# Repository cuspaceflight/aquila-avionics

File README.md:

# Aquila Avionics
Schematics and firmware for Aquila flight computer.

## Functions
* **Altimetry** - Accurately estimate altitude with barometer, GPS and accelerometer
* **Recovery** - Activate pyrotechnics to deploy parachute stages at appropriate points during descent
*  **Data logging** - Log altitude data and other parameters for post-flight analysis
* **Telemetry** - Transmit data to a ground station during flight as a backup should the vehicle be lost
* **Location** - Continually transmit location after landing to aid finding the vehicle

## Specifications
* **Mass** -  2kg
* **Acceleration** - 30g
* **Altitude** - 150km
* **Speed** - 1500m/s
* **Flexibility** - Exact flight and recovery profile is TBC
*  **Budget** - �150

# Overview
What follows here is a very brief overview of the design, broken down by component. It's aim is to familiarise the reader with what this project includes and some of the decisions made.
## Batteries
The computer is designed to run from two 18650 Li-Ions in series. A battery management chip monitors the cell voltages and automatically balances them if necessary. There is no onboard charger, so batteries must be charged separately before installation/flights. Ideally cells with built-in under-volt protection should be used. The battery holders are physically mounted to the board (but will be mechanically supported by additional hardware). Power can be switched on and off via a screw terminal.  To connect the batteries to the rest of the board, a jumper is secured between the two terminals. A potential divider allows the microcontroller to directly monitor the battery voltages.

Additionally, a 3V CR2032 type cell is mounted to the board. This maintains real time clocks in the microcontroller and GPS receiver, improving resilience against power cycle events during flight.
## Power supplies
The board has two power supplies: 3.3V 3A and 5V 3A. The 3.3V supply powers most of the electronics on the board and is permanently on. The 5V supply is dedicated to pyrotechnics and servos as required by the recovery system. It is switched on and off by the microcontroller to conserve power when not needed and as a safety layer. A terminal is provided for an external safety switch. When shorted, this terminal disables the pyro power supply, eliminating the risk of unintentionally activating pyrotechnics during any activities leading up to launch.
## Sensors
### Barometer
A barometer is mounted on the board to measure atmospheric pressure. This is particularly useful during descent to deploy parachute stages at appropriate altitudes close to the ground. The model used is a MS5611-01BA03. It has a resolution on the order of tenths of millibar, but a minimum pressure of 10 millibar limits it's usefulness to below 30 km altitude.
### GPS
A U-blox MAX-M8Q receiver is included for completeness. CoCom regulations limit the operation of civilian GPS chips faster than 1000 knots (~500 m/s) and above 18 km, both of which will be exceeded early in Griffin's flight profile. Therefore the GPS will not be relied on for navigational purposes, but purely for data collection. It may be the case that once the rocket slows below 1000 knots near apogee, a fix can once again be acquired. This is uncertain as the manufacturer does not specify behaviour at these extremes.

An additional Low-Noise Amplifier and band-pass filter are included in the signal path as antenna challenges and telemetry radio interference will degrade signal quality.
### Accelerometer
The most important sensor for navigation and apogee deployment is the accelerometer. An inertial navigation system will be implemented to estimate the vehicle's velocity and altitude based on accelerometer readings. The double integration of acceleration to velocity leads to errors on the order of time squared, so it is imperative the accelerometer readings are low noise and very stable. Combined with this requirement, a high g range is required as the rocket will accelerate at up to 30g at some points.  An Analog Devices ADXL357 is chosen. It boasts 20 bit resolution, ultra-low noise and high bias stability with a range of +/- 40g.
## Telemetry
An Si4463 radio transceiver provides a bi-directional radio link with a ground station. This will be useful for configuring the computer during launch preparations as well as backing up as much data as possible should the vehicle be lost. A secondary purpose for the radio will be locating the vehicle after a successful recovery. The current setup is designed for operation in the 915 MHz ISM band, subject to regulatory compliance.
## Interfaces
Connectors on the board include: 
* **female SMA** for GPS antenna
* **female SMA** for telemetry antenna
* **6-way Molex Nano-Fit** for a separate, remote, barometer, in case structural limitations prevent the avionics bay being vented to the atmosphere
* **6-way Molex Nano-Fit** for up to four servo motors
* **4x 2-way screw terminal** for up to four pyrotechnics
* **Micro USB** for programming and serial communication

The pyro channels can provide 5V at 1A continuous as limited by the FETs, 3A peak as limited by the power supply. They also include individual continuity measurement by draining approximately 50uA through the pyro.
## Microcontroller
A Teensy 4.1 was selected as the microcontroller. It is based around an ARM Cortex-M7 running at 600MHz. The first reason for this choice is that it includes many features we would only have to implement ourselves such as a real time clock, MicroSD storage, USB interface etc. Secondly, it is compatible with the Arduino ecosystem, granting access to many existing libraries and improving access to the firmware for CUSF members.
## Antennas
Antennas are an area of ongoing research, hence nothing has been included in this repo yet. Carbon-fibre reinforced polymer (CFRP) construction precludes antennas being mounted inside the rocket body, and extreme aerodynamic and aerothermal loads make any kind of protruding antenna impossible. This leaves the only possible solution as conformal patch antenna arrays. Methods to design and optimise these antennas and feed networks are currently being developed. See <https://github.com/cuspaceflight/aperture>.

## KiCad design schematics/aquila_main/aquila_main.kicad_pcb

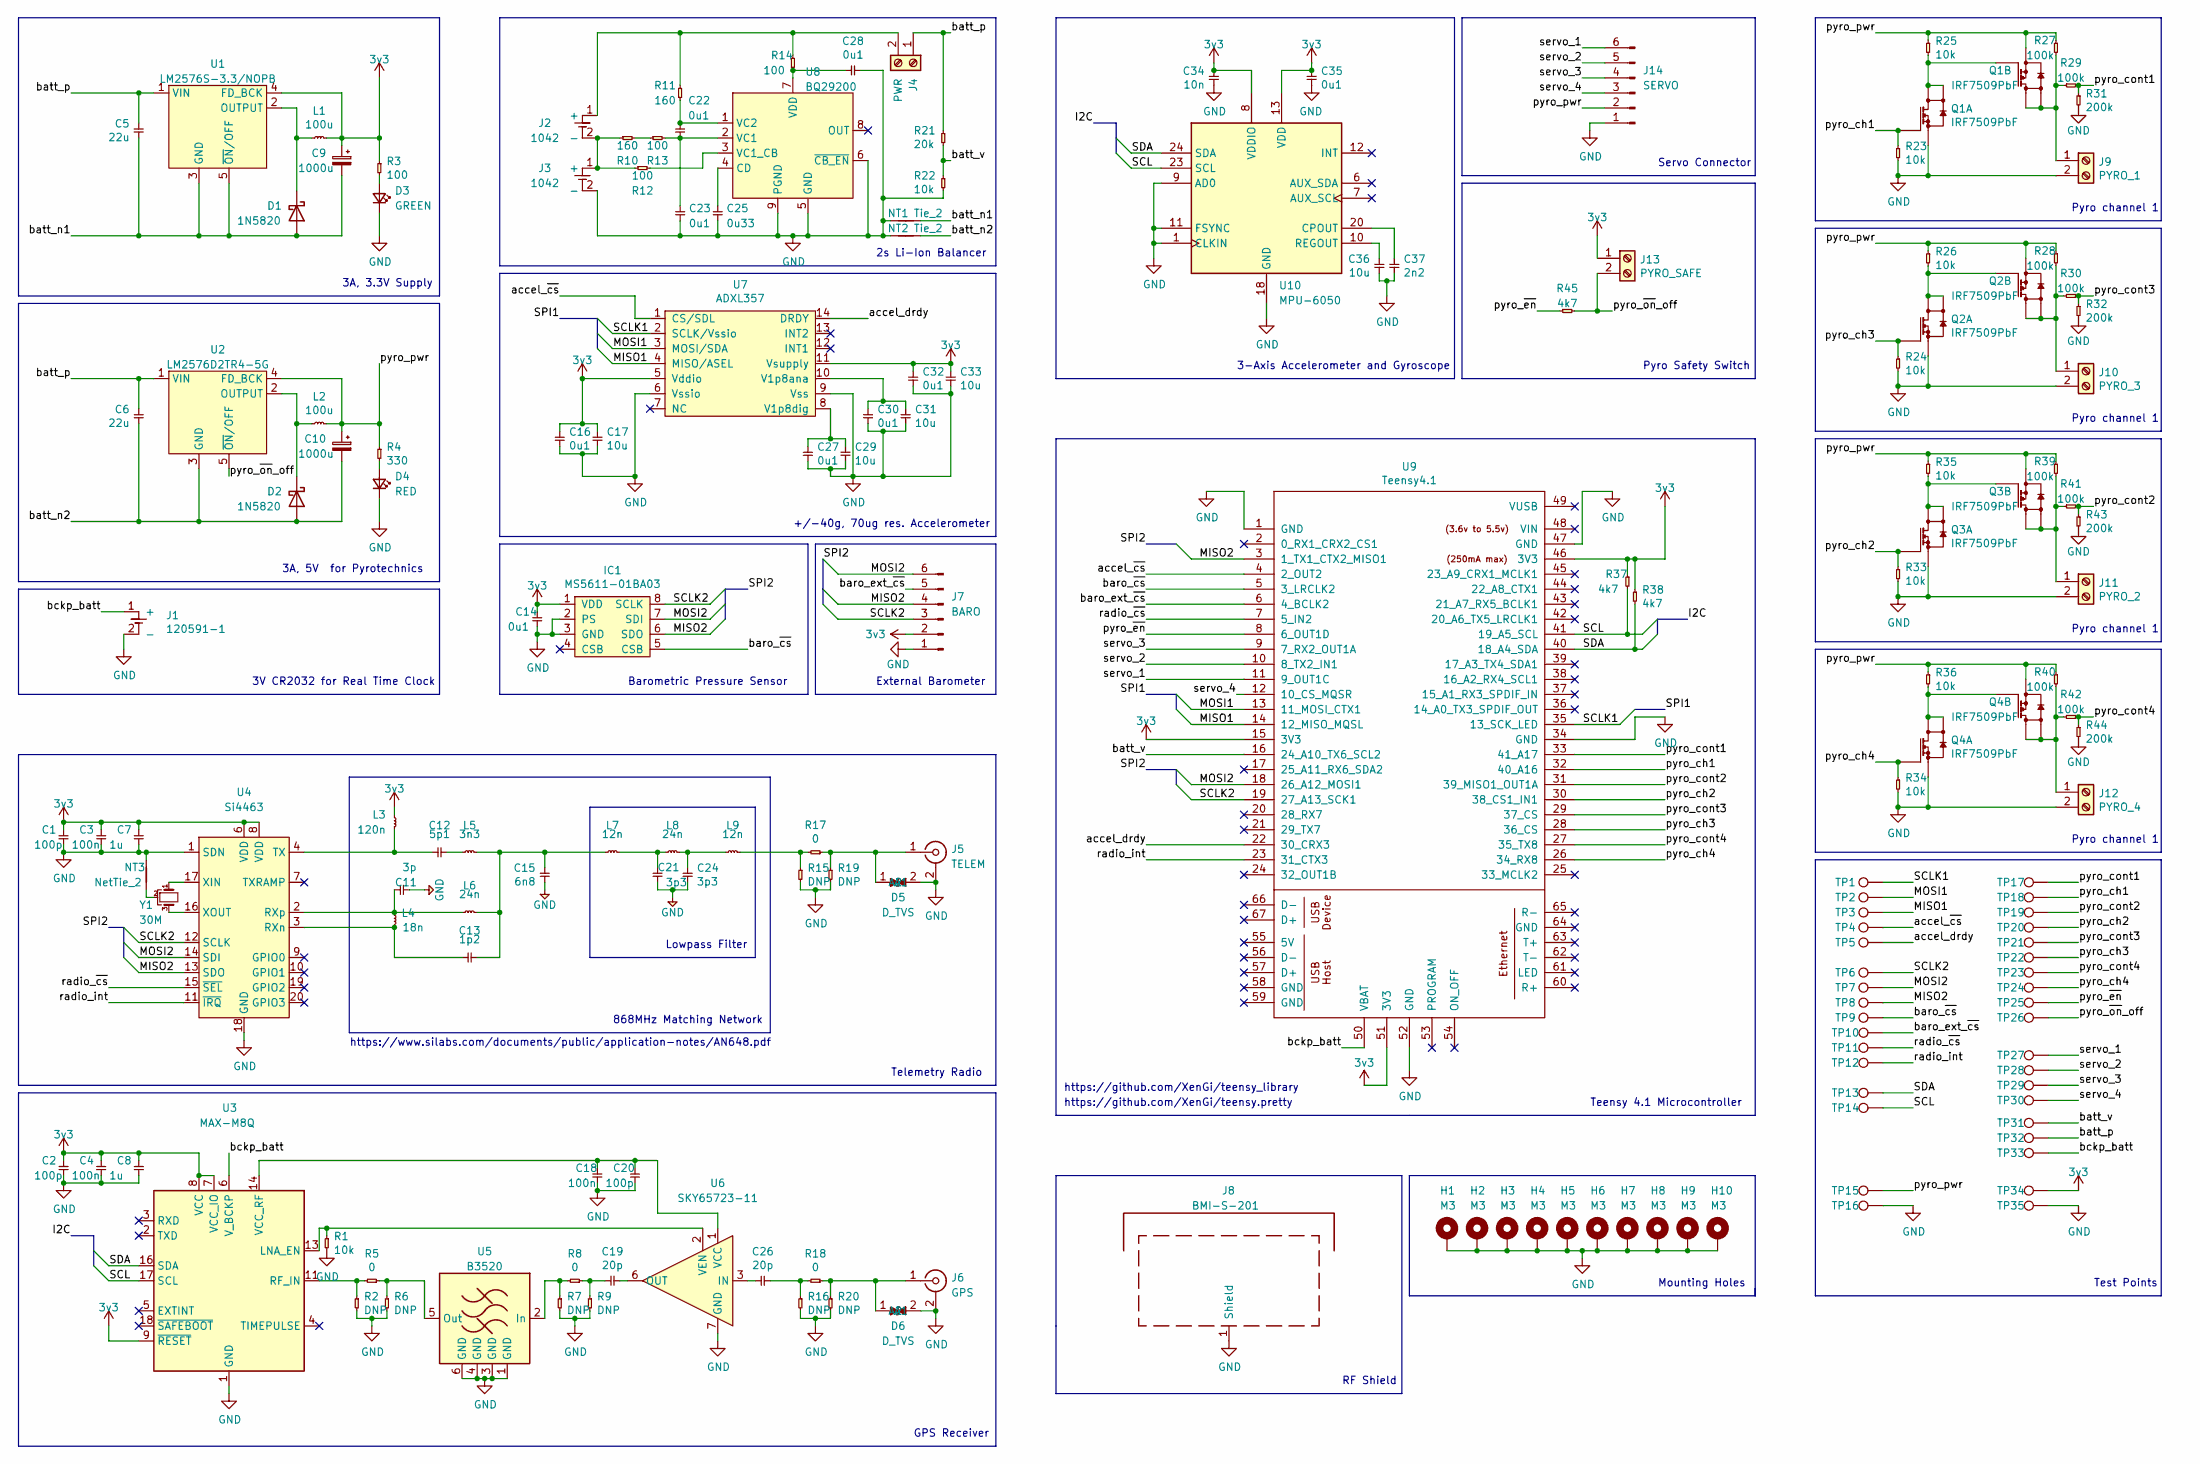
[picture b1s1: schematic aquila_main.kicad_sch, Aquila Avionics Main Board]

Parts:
C1, C2, C20: 100p; C_0402_1005Metric
C3, C4, C18: 100n; C_0402_1005Metric
C5, C6: 22u; CP_Radial_D6.3mm_P2.50mm; Farnell 9452710
C7, C8: 1u; C_0402_1005Metric
C9, C10: 1000u; CP_Radial_D8.0mm_P3.50mm; Farnell 2760327
C11: 3p; C_0402_1005Metric; Farnell 1758933
C12: 5p1; C_0402_1005Metric; Farnell 2781439
C13: 1p2; C_0402_1005Metric; Farnell 3369062
C14, C16, C22, C23, C27, C28, C30, C32, C35: 0u1; C_0402_1005Metric
C15: 6n8; C_0402_1005Metric; Farnell 2627370
C17, C29, C31, C33, C36: 10u; C_0402_1005Metric
C19, C26: 20p; C_0402_1005Metric
C21, C24: 3p3; C_0402_1005Metric; Farnell 2627406
C25: 0u33; C_0402_1005Metric
C34: 10n; C_0402_1005Metric
C37: 2n2; C_0402_1005Metric
D1, D2: 1N5820; D_DO-201AD_P15.24mm_Horizontal; Farnell 2317410
D3: GREEN; D_0603_1608Metric; Farnell 3796304
D4: RED; D_0603_1608Metric; Farnell 3796306
D5, D6: D_TVS; D_0402_1005Metric; Farnell 2368169
H1, H2, H3, H4, H5, H6, H7, H8, H9, H10: M3; MountingHole_3.2mm_M3_DIN965_Pad
IC1: MS5611-01BA03; MS5611; Farnell 2362662
J1: 120591-1; DigiKey A99328-ND
J2, J3: 1042; DigiKey 36-1042P-ND
J4: PWR; MP_2.54_screw_terminal_2x1; Farnell 3817460
J5: TELEM; SMA_VERT; Mouser 960-PCB.SMAFST.J.AHT
J6: GPS; SMA_VERT; Mouser 960-PCB.SMAFST.J.AHT
J7: BARO; molex_nano_fit_x6_105310-1106; Farnell 2820682
J8: BMI-S-201; Farnell 2497715
J9: PYRO_1; MP_2.54_screw_terminal_2x1; Farnell 3817460
J10: PYRO_3; MP_2.54_screw_terminal_2x1; Farnell 3817460
J11: PYRO_2; MP_2.54_screw_terminal_2x1; Farnell 3817460
J12: PYRO_4; MP_2.54_screw_terminal_2x1; Farnell 3817460
J13: PYRO_SAFE; MP_2.54_screw_terminal_2x1; Farnell 3817460
J14: SERVO; molex_nano_fit_x6_105310-1106; Farnell 2820682
L1, L2: 100u; L_MP0028_124_125_127; Farnell 2288307
L3: 120n; L_0402_1005Metric; Farnell 3471254
L4: 18n; L_0402_1005Metric; Farnell 1343084
L5: 3n3; L_0402_1005Metric; Farnell 1343068
L6, L8: 24n; L_0402_1005Metric; Farnell 3263549
L7, L9: 12n; L_0402_1005Metric; Farnell 1343082
NT1, NT2: Tie_2; NetTie-2_THT_Pad1.0mm
NT3: NetTie_2; NetTie-2_SMD_Pad0.5mm
Q1, Q2, Q3, Q4: IRF7509PbF; Farnell 1611421
R1, R22, R23, R24, R25, R26, R33, R34, R35, R36: 10k; R_0402_1005Metric
R2, R6, R7, R9, R15, R16, R19, R20: DNP; R_0402_1005Metric
R3, R12, R13, R14: 100; R_0402_1005Metric
R4: 330; R_0402_1005Metric
R5, R8, R17, R18: 0; R_0402_1005Metric
R10, R11: 160; R_0402_1005Metric
R21: 20k; R_0402_1005Metric
R27, R28, R29, R30, R39, R40, R41, R42: 100k; R_0402_1005Metric
R31, R32, R43, R44: 200k; R_0402_1005Metric
R37, R38, R45: 4k7; R_0402_1005Metric
TP1, TP2, TP3, TP4, TP5, TP6, TP7, TP8, TP9, TP10, TP11, TP12, TP13, TP14, TP15, TP16, TP17, TP18, TP19, TP20, TP21, TP22, TP23, TP24, TP25, TP26, TP27, TP28, TP29, TP30, TP31, TP32, TP33, TP34, TP35: TestPoint; TestPoint_Pad_D1.0mm
U1: LM2576S-3.3/NOPB; TO-236_5; Farnell 3008143
U2: LM2576D2TR4-5G; TO-236_5; Farnell 2534166
U3: MAX-M8Q
U4: Si4463; QFN-20-1EP_4x4mm_P0.5mm_EP2.6x2.6mm_ThermalVias; DigiKey 336-4346-1-ND
U5: B3520; DigiKey 495-2363-1-ND
U6: SKY65723-11; SKY65723-81; Mouser 873-SKY65723-81
U7: ADXL357; DigiKey 505-ADXL357BEZ-ND
U8: BQ29200; VSOP-8; Farnell 2383074
U9: Teensy4.1; Teensy41; DigiKey 223-1622-1-ND
U10: MPU-6050; InvenSense_QFN-24_4x4mm_P0.5mm; Farnell 3769961
Y1: 30M; crystal_ABM8; Farnell 3228351

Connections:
+3V3: C1.1, C2.1, C3.1, C4.1, C7.1, C8.1, C9.1, C14.1, C16.1, C17.1, C32.1, C33.1, C34.1, C35.1, IC1.1 (VDD), J7.2, J13.1, L1.2, L3.1, R3.1, R37.1, R38.1, TP34.1, U1.4 (FD_BCK), U3.7 (VCC_IO), U3.8 (VCC), U3.9 (~RESET), U4.6 (VDD), U4.8 (VDD), U7.5 (Vddio), U7.11 (Vsupply), U9.15 (3V3), U9.46 (3V3), U9.51 (3V3), U10.8 (VDDIO), U10.13 (VDD)
/MISO1: TP3.1, U7.4 (MISO/ASEL), U9.14 (12_MISO_MQSL)
/MISO2: IC1.6 (SDO), J7.4, TP8.1, U4.13 (SDO), U9.3 (1_TX1_CTX2_MISO1)
/MOSI1: TP2.1, U7.3 (MOSI/SDA), U9.13 (11_MOSI_CTX1)
/MOSI2: IC1.7 (SDI), J7.6, TP7.1, U4.14 (SDI), U9.18 (26_A12_MOSI1)
/SCL: R37.2, TP14.1, U3.17 (SCL), U9.41 (19_A5_SCL), U10.23 (SCL)
/SCLK1: TP1.1, U7.2 (SCLK/Vssio), U9.35 (13_SCK_LED)
/SCLK2: IC1.8 (SCLK), J7.3, TP6.1, U4.12 (SCLK), U9.19 (27_A13_SCK1)
/SDA: R38.2, TP13.1, U3.16 (SDA), U9.40 (18_A4_SDA), U10.24 (SDA)
/accel_drdy: TP5.1, U7.14 (DRDY), U9.22 (30_CRX3)
/accel_~cs: TP4.1, U7.1 (CS/SDL), U9.4 (2_OUT2)
/baro_ext_~cs: J7.5, TP10.1, U9.6 (4_BCLK2)
/baro_~cs: IC1.5 (CSB), TP9.1, U9.5 (3_LRCLK2)
/batt_n1: C5.2, C9.2, D1.2 (A), NT1.2, U1.3 (GND), U1.5 (~ON/OFF)
/batt_n2: C6.2, C10.2, D2.2 (A), NT2.2, U2.3 (GND)
/batt_p: C5.1, C6.1, J4.1, R21.1, TP32.1, U1.1 (VIN), U2.1 (VIN)
/batt_v: R21.2, R22.1, TP31.1, U9.16 (24_A10_TX6_SCL2)
/bckp_batt: J1.1 (+), TP33.1, U3.6 (V_BCKP), U9.50 (VBAT)
/pyro_ch1: Q1.2 (G1), R23.1, TP18.1, U9.32 (40_A16)
/pyro_ch2: Q3.2 (G1), R33.1, TP20.1, U9.30 (38_CS1_IN1)
/pyro_ch3: Q2.2 (G1), R24.1, TP22.1, U9.28 (36_CS)
/pyro_ch4: Q4.2 (G1), R34.1, TP24.1, U9.26 (34_RX8)
/pyro_cont1: R29.2, R31.1, TP17.1, U9.33 (41_A17)
/pyro_cont2: R41.2, R43.1, TP19.1, U9.31 (39_MISO1_OUT1A)
/pyro_cont3: R30.2, R32.1, TP21.1, U9.29 (37_CS)
/pyro_cont4: R42.2, R44.1, TP23.1, U9.27 (35_TX8)
/pyro_pwr: C10.1, J14.2, L2.2, Q1.3 (S2), Q2.3 (S2), Q3.3 (S2), Q4.3 (S2), R4.1, R25.1, R26.1, R27.1, R28.1, R35.1, R36.1, R39.1, R40.1, TP15.1, U2.4 (FD_BCK)
/pyro_~en: R45.1, TP25.1, U9.8 (6_OUT1D)
/pyro_~on_off: J13.2, R45.2, TP26.1, U2.5 (~ON/OFF)
/radio_int: TP12.1, U4.11 (~IRQ), U9.23 (31_CTX3)
/radio_~cs: TP11.1, U4.15 (~SEL), U9.7 (5_IN2)
/servo_1: J14.6, TP27.1, U9.11 (9_OUT1C)
/servo_2: J14.5, TP28.1, U9.10 (8_TX2_IN1)
/servo_3: J14.4, TP29.1, U9.9 (7_RX2_OUT1A)
/servo_4: J14.3, TP30.1, U9.12 (10_CS_MQSR)
GND: C1.2, C2.2, C3.2, C4.2, C7.2, C8.2, C11.2, C14.2, C15.2, C16.2, C17.2, C18.2, C20.2, C21.2, C23.1, C24.2, C25.1, C27.2, C28.2, C29.2, C30.2, C31.2, C32.2, C33.2, C34.2, C35.2, C36.2, C37.2, D3.1 (K), D4.1 (K), D5.2 (A2), D6.2 (A2), H1.1, H2.1, H3.1, H4.1, H5.1, H6.1, H7.1, H8.1, H9.1, H10.1, IC1.2 (PS), IC1.3 (GND), J1.2 (-), J3.2 (-), J5.2 (Ext), J6.2 (Ext), J7.1, J8.1 (Shield), J9.2, J10.2, J11.2, J12.2, J14.1, NT1.1, NT2.1, NT3.2, Q1.1 (S1), Q2.1 (S1), Q3.1 (S1), Q4.1 (S1), R1.2, R2.2, R6.2, R7.2, R9.2, R15.2, R16.2, R19.2, R20.2, R22.2, R23.2, R24.2, R31.2, R32.2, R33.2, R34.2, R43.2, R44.2, TP16.1, TP35.1, U3.1 (GND), U3.10 (GND), U3.12 (GND), U4.1 (SDN), U4.18 (GND), U4.21 (GND), U5.1 (GND), U5.3 (GND), U5.4 (GND), U5.6 (GND), U6.7 (GND), U7.6 (Vssio), U7.9 (Vss), U8.5 (GND), U8.6 (~CB_EN), U8.9 (PGND), U9.1 (GND), U9.34 (GND), U9.47 (GND), U9.52 (GND), U10.1 (CLKIN), U10.9 (AD0), U10.11 (FSYNC), U10.18 (GND)
unnamed: C11.1, L4.1, L6.1, U4.2 (RXp)
unnamed: C12.1, L3.2, U4.4 (TX)
unnamed: C12.2, L5.1
unnamed: C13.1, L4.2, U4.3 (RXn)
unnamed: C13.2, C15.1, L5.2, L6.2, L7.1
unnamed: C18.1, C20.1, U3.14 (VCC_RF), U6.1 (VCC)
unnamed: C19.1, R8.1, R9.1
unnamed: C19.2, U6.6 (OUT)
unnamed: C21.1, L7.2, L8.1
unnamed: C22.1, C23.2, R13.2, U8.2 (VC1)
unnamed: C22.2, R11.1, U8.1 (VC2)
unnamed: C24.1, L8.2, L9.1
unnamed: C25.2, U8.4 (CD)
unnamed: C26.1, U6.3 (IN)
unnamed: C26.2, R16.1, R18.2
unnamed: C27.1, C29.1, U7.8 (V1p8dig)
unnamed: C28.1, R14.1, U8.7 (VDD)
unnamed: C30.1, C31.1, U7.10 (V1p8ana)
unnamed: C36.1, U10.10 (REGOUT)
unnamed: C37.1, U10.20 (CPOUT)
unnamed: D1.1 (K), L1.1, U1.2 (OUTPUT)
unnamed: D2.1 (K), L2.1, U2.2 (OUTPUT)
unnamed: D3.2 (A), R3.2
unnamed: D4.2 (A), R4.2
unnamed: D5.1 (A1), J5.1 (In), R17.1, R19.1
unnamed: D6.1 (A1), J6.1 (In), R18.1, R20.1
unnamed: J2.1 (+), J4.2, R11.2, R14.2
unnamed: J2.2 (-), J3.1 (+), R10.1, R12.1
unnamed: J9.1, Q1.5 (D2), Q1.6 (D2), R27.2, R29.1
unnamed: J10.1, Q2.5 (D2), Q2.6 (D2), R28.2, R30.1
unnamed: J11.1, Q3.5 (D2), Q3.6 (D2), R39.2, R41.1
unnamed: J12.1, Q4.5 (D2), Q4.6 (D2), R40.2, R42.1
unnamed: L9.2, R15.1, R17.2
unnamed: Q1.4 (G2), Q1.7 (D1), Q1.8 (D1), R25.2
unnamed: Q2.4 (G2), Q2.7 (D1), Q2.8 (D1), R26.2
unnamed: Q3.4 (G2), Q3.7 (D1), Q3.8 (D1), R35.2
unnamed: Q4.4 (G2), Q4.7 (D1), Q4.8 (D1), R36.2
unnamed: R1.1, U3.13 (LNA_EN), U6.2 (VEN)
unnamed: R2.1, R5.2, U3.11 (RF_IN)
unnamed: R5.1, R6.1, U5.5 (Out)
unnamed: R7.1, R8.2, U5.2 (In)
unnamed: R10.2, R13.1
unnamed: R12.2, U8.3 (VC1_CB)
unnamed: U4.16 (XOUT), Y1.3
unnamed: U4.17 (XIN), Y1.1
unnamed: NT3.1, Y1.2

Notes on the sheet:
Pyro channel 1
Barometric Pressure Sensor
Telemetry Radio
Test Points
Mounting Holes
GPS Receiver
Teensy 4.1 Microcontroller
https://www.silabs.com/documents/public/application-notes/AN648.pdf
External Barometer
+/-40g, 70ug res. Accelerometer
https://github.com/XenGi/teensy_library
3-Axis Accelerometer and Gyroscope
Servo Connector
3A, 5V for Pyrotechnics
RF Shield
3V CR2032 for Real Time Clock
2s Li-Ion Balancer
868MHz Matching Network
Lowpass Filter
https://github.com/XenGi/teensy.pretty
Pyro Safety Switch
3A, 3.3V Supply

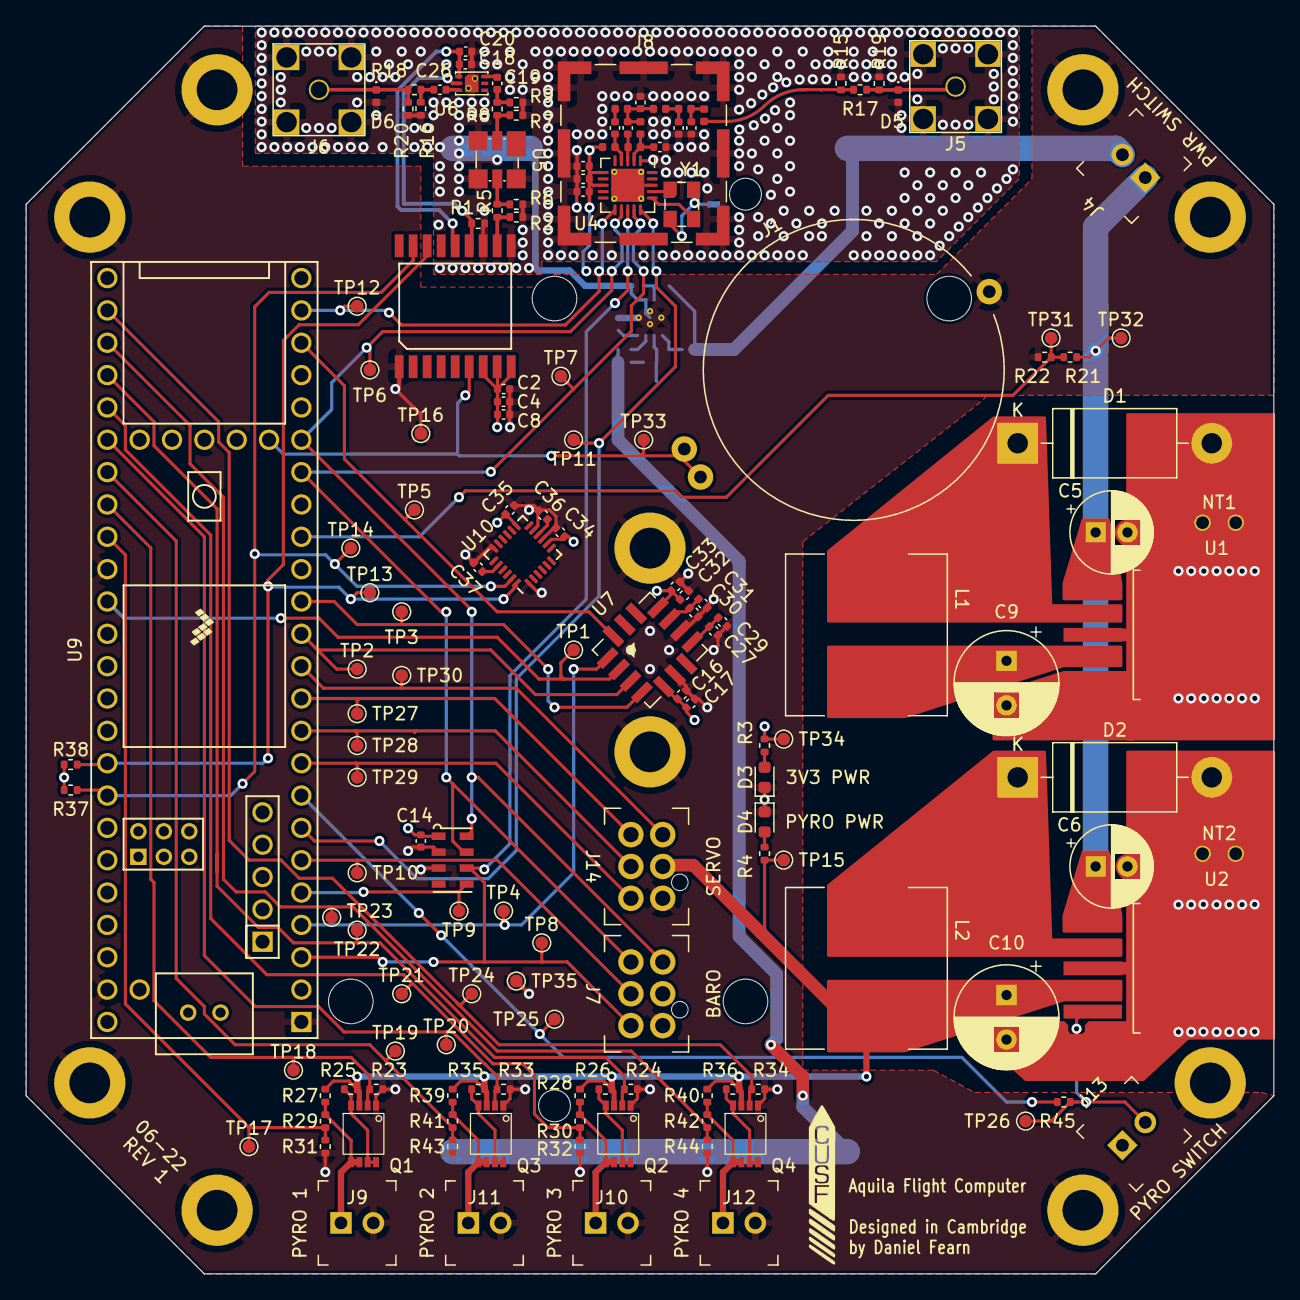
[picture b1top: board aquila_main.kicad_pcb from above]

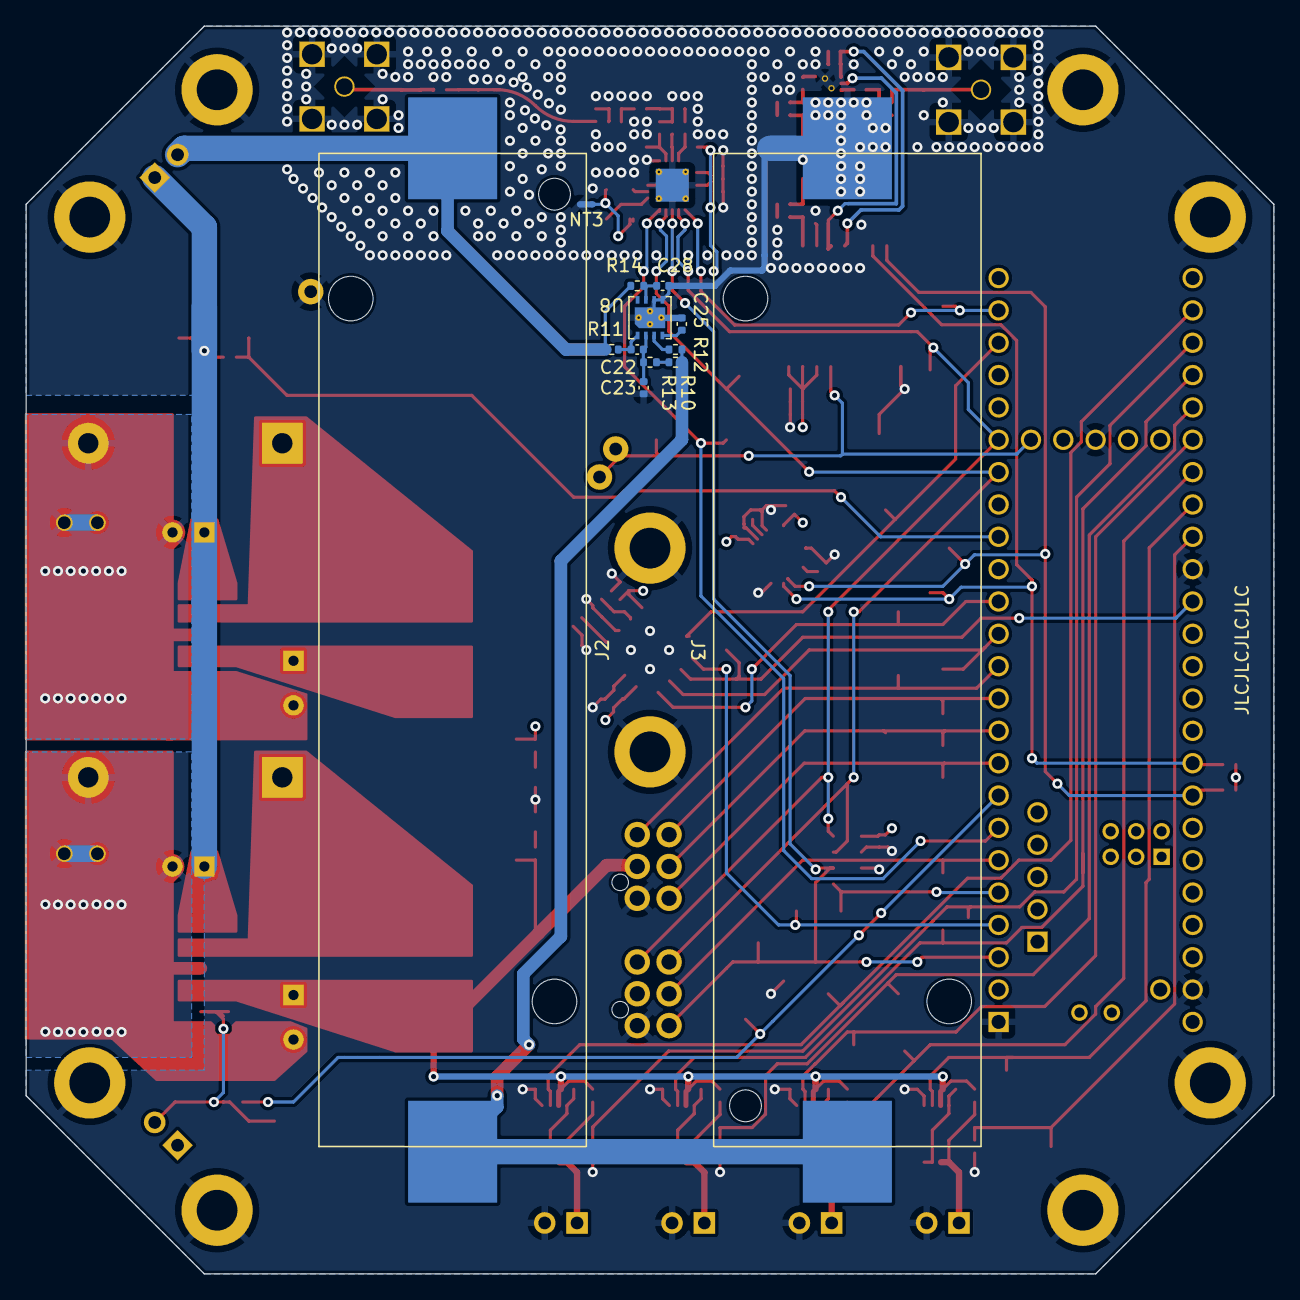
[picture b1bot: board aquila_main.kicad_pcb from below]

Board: 4 copper layers, 98.0 x 98.0 mm, 175 parts (13 on the bottom side), 82 nets.

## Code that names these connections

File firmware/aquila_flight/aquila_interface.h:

#pragma once

#include "Arduino.h"
#include "SPI.h"
#include "Wire.h"
#include "rtc.h"
#include "adxl357.h"
#include "ms56_11_07.h"
#include "mpu6050.h"

#define pin_accel_cs 2
#define pin_accel_drdy 30

#define pin_baro_cs 3
#define pin_baro_ext_cs 4

#define pin_batt_v 24

#define pin_pyro_arm 6
#define pin_pyro_cont1 41
#define pin_pyro1 40
#define pin_pyro_cont2 39
#define pin_pyro2 38
#define pin_pyro_cont3 37
#define pin_pyro3 36
#define pin_pyro_cont4 35
#define pin_pyro4 34


class AQUILA {
  public:
    void begin();

    void rtc_datetime(char* outstr);
    uint32_t rtc_unix();

    void update_accel();
    float get_accel_x();
    float get_accel_y();
    float get_accel_z();

    bool poll_baro_ext();
    float get_ext_pressure();
    float get_ext_temperature();

    bool poll_baro_int();
    float get_int_pressure();
    float get_int_temperature();

    void update_imu();
    float get_imu_accel_x();
    float get_imu_accel_y();
    float get_imu_accel_z();
    float get_imu_gyro_x();
    float get_imu_gyro_y();
    float get_imu_gyro_z();

    float get_batt_voltage();

    void arm_pyro();
    void disarm_pyro();
    bool pyro_is_armed();
    bool pyro_continuity(uint8_t pyro_number);
    bool fire_pyro(uint8_t pyro_number);

  private:
    TEENSY_RTC rtc;
    ADXL357 accel;
    MS56_11_07 baro_ext;
    MS56_11_07 baro;
    MPU6050 imu;

    bool pyro_armed;
};

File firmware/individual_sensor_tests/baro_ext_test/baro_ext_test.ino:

/*
 * Teensy 4.1
 * 
 * MS5607 on SPI1 port:
 * MOSI - 26
 * MISO - 1
 * SCLK - 27
 * CS - 4
 * 
 */

 #include <SPI.h>

const bool loop_mode = true;

const int cs = 4;
const int MOSI2 = 26;
const int MISO2 = 1;
const int SCLK2 = 27;

float c1;
float c2;
float c3;
float c4;
float c5;
float c6;

uint32_t D1;
uint32_t D2;

float smoothed = 0;

void setup() {
  
  Serial.begin(9600);
  
  SPI1.begin();

  

  pinMode(cs, OUTPUT);
  digitalWrite(cs, HIGH);

  delay(500);

  if(loop_mode) {
    send_baro_command(0x1E);
    delay(500);
    c1 = read_baro_register(0xA2, 2);
    c2 = read_baro_register(0xA4, 2);
    c3 = read_baro_register(0xA6, 2);
    c4 = read_baro_register(0xA8, 2);
    c5 = read_baro_register(0xAA, 2);
    c6 = read_baro_register(0xAC, 2);
  } else {
    // send reset command
    Serial.println("Sending reset:");
    Serial.println(send_baro_command(0x1E));
    delay(500);
  
    
  
    // read 16 bit PROM value
    Serial.println("Requesting PROM calibration values:");
    c1 = read_baro_register(0xA2, 2);
    c2 = read_baro_register(0xA4, 2);
    c3 = read_baro_register(0xA6, 2);
    c4 = read_baro_register(0xA8, 2);
    c5 = read_baro_register(0xAA, 2);
    c6 = read_baro_register(0xAC, 2);
    Serial.print(c1);
    Serial.print(", ");
    Serial.print(c2);
    Serial.print(", ");
    Serial.print(c3);
    Serial.print(", ");
    Serial.print(c4);
    Serial.print(", ");
    Serial.print(c5);
    Serial.print(", ");
    Serial.println(c6);
  
    delay(2000);
  
    Serial.println("Sending pressure conversion command and reading ADC");
    send_baro_command(0x48);
    D1 = read_baro_register(0x00, 3);
    D1 = 6472300;
    Serial.println(D1);
    Serial.println("Sending temperature conversion command and reading ADC");
    send_baro_command(0x58);
    D2 = read_baro_register(0x00, 3);
    D2 = 8370462;
    Serial.println(D2);
  
    Serial.println("Calculating temperature:");
    int64_t dT = D2 - (c5*256);
    Serial.println(dT);
    int64_t temp = 2000 + ((dT*c6)/8388608);
    Serial.println(temp/100.0);
  
    Serial.println("Calculating pressure:");
    float off = (c2*131072) + (c4 * dT)/64;
    Serial.println(off);
    int64_t sens = c1*65536 + (c3 * dT)/128;
    Serial.println(sens);
    int32_t p = (((D1 * sens)/2097152) - off)/32768;
    Serial.println(p/100.0);

  }
}

void loop() {
  send_baro_command(0x48);
  D1 = read_baro_register(0x00, 3);
  send_baro_command(0x58);
  D2 = read_baro_register(0x00, 3);

  int64_t dT = D2 - (c5*256);
  int64_t temp = 2000 + ((dT*c6)/8388608);

  float off = (c2*131072) + (c4 * dT)/64;
  int64_t sens = c1*65536 + (c3 * dT)/128;
  int32_t p = (((D1 * sens)/2097152) - off)/32768;

  // conditioning to make nice plots
  int32_t dp = p - 99100;
  smoothed = smoothed * 0.9 + p*0.1;
  Serial.println(smoothed);
}

unsigned int send_baro_command(byte baro_command){
  SPI1.beginTransaction(SPISettings(4000000, MSBFIRST, SPI_MODE0));
  digitalWrite(cs, LOW);
  unsigned int result = SPI1.transfer(baro_command);
  delay(10);
  digitalWrite(cs, HIGH);
  SPI1.endTransaction();

  return result;
}

unsigned int read_baro_register(byte target_register, int num_bytes) {
  SPI1.beginTransaction(SPISettings(4000000, MSBFIRST, SPI_MODE0));
  digitalWrite(cs, LOW);
  SPI1.transfer(target_register);
  unsigned int result = SPI1.transfer(0x00);
  num_bytes--;
  while(num_bytes > 0){
    result = result << 8;
    result = result | SPI1.transfer(0x00);
    num_bytes--;
  }
  digitalWrite(cs, HIGH);
  SPI1.endTransaction();

  return result;
}

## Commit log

2022-03-06 added symbol and footprint for ADXL357
2022-03-06 added connections for accelerometer
2022-03-10 added symbol and footprint for RTC bat. holder
2022-03-10 added connections for barometer
2022-03-11 added DXF of flange for reference
2022-03-12 added dimensions to flange dxf
2022-03-13 added connections for telemetry radio
2022-03-17 sketched potential board shape
2022-03-17 added .gitignore
2022-03-17 fixed untracked files
2022-03-18 updated to KiCad 6
2022-03-19 added connections for GPS
2022-03-19 added power indicator LEDs
2022-03-20 removed dependence on deprecated symbol library
2022-03-21 added battery holders and balancer
2022-03-28 added telemetry radio matching network
2022-03-28 fixed net label formatting
2022-03-29 added connections for Teensy uC
2022-03-29 designed out unobtainable components
2022-03-29 added connector for optional external barometer
2022-03-29 created footprint for LM2576
2022-03-29 copied in Teensy libraries
2022-03-29 created footprints for RF components
2022-03-29 added mounting holes
2022-03-29 added I2C pullups
2022-03-29 added Pi pad to telem line
2022-03-29 added footprint for BQ29200
2022-03-30 added RF shield
2022-03-31 changed to 868MHz matching on radio
2022-03-31 added pyro safety switch
2022-03-31 added footprint for crystal
2022-04-01 added order numbers and footprints to small parts
2022-04-01 changed PCB shape to make better use of space
2022-04-01 changed pyro power to 5V
2022-04-01 added connector for servos
2022-04-01 assigned all remaining footprints
2022-04-02 initialised PCB layout
2022-04-02 preliminary placement of components
2022-04-03 placed all components and traces
2022-04-04 fixed relevant DRC errors
2022-04-04 added silkscreen logo etc
2022-04-05 minor adjustments
2022-06-16 added test points, redesigned power supplies
2022-06-16 added dimensions for mounting holes
2022-07-28 added manufacture files and BoM
2022-07-29 fixed mistake in bom
2022-07-30 designed PCB support
2022-08-20 first signs of firmware
2022-08-27 expanded barometer class to support different models
2022-08-28 added class for real-time clock
2022-08-28 updated barometer test condition
2022-08-28 made the testing output more interesting
2022-08-28 added battery voltage measurement
2022-08-31 added class for MPU6050
2022-09-10 added pyro controls
2022-09-12 added inertial sensor calibration program
2022-10-09 moved aquila_interface to a library
2022-10-09 renamed some files and created the actual flight program file
2022-10-09 added timing loops
2022-10-09 removed debugging printing
2022-10-09 implemented serial commands
2022-10-09 implemented servo control
2022-10-10 added requirement tracking comments
2022-10-10 added accel interrupt handler
2022-10-10 added transition conditions for some states
2022-10-11 set servo positions
2022-10-15 added (inefficient) SD logging
2022-10-23 improved datalogging
2022-10-23 removed unused code
2022-10-26 fixed barometer timing bug
2022-10-26 moved logging time to before reading sensors
2022-11-06 implemented nosecone and parachute actuation
2022-11-06 added two point calibration for mpu6050 sensor
2022-11-13 added safe pyro arming
2023-02-05 added landing detection
2023-02-12 test Daniel Ciesla
2023-02-12 Undo Test - Success
2023-02-19 added HIL testing
2023-02-19 Changes for si4463
2023-02-19 included files for generating HIL tests
2023-02-19 More si4463 changes
2023-02-19 updated .gitignore
2023-02-20 Added lora cpp and h files, wrote 3 functions
2023-02-20 corrections
2023-02-20 added transmit function, needs testing
2023-02-20 Added comments and corrections
2023-02-22 Added null pointer return
2023-02-22 added a semicolon
2023-03-12 Added lora read/write
2023-05-10 radio link established
2023-05-10 updated comments
2023-05-27 working first pass at telemetry
2023-08-11 fit more data into telem packet
2023-08-13 tracked down SD logging bug that was causing crash on pyro arm
2023-08-13 added command to calibrate altimeter
2023-08-13 added documentation as markdown
2023-08-13 fixed table formatting
2023-08-13 changed parachute deploy to altitude rather than time
2023-08-13 made HIL testing easier to run
2023-08-13 added pyro disarm on landing
2023-08-13 stop integrating on landing
2023-08-13 moved command handling to separate function
2023-08-14 implemented telecommand
2023-08-19 added human readable and csv serial modes
2023-09-03 fixed pyro firing bug
2023-09-03 all four pyros now fired at apogee
2023-09-03 telemetry now sends system microseconds rather than unix time
2023-09-03 designed mounting hardware for LoRa module
2023-09-09 created GUI program for ground station
2023-09-09 tweaked ground station firmware to work with GUI program
2023-09-09 changed flight program to not overwrite data
2023-09-18 removed gcode
2023-09-18 removed last gcode
